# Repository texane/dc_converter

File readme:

updown DC converter. from 12V to 3.4V 5.2V 12V 19.6V.

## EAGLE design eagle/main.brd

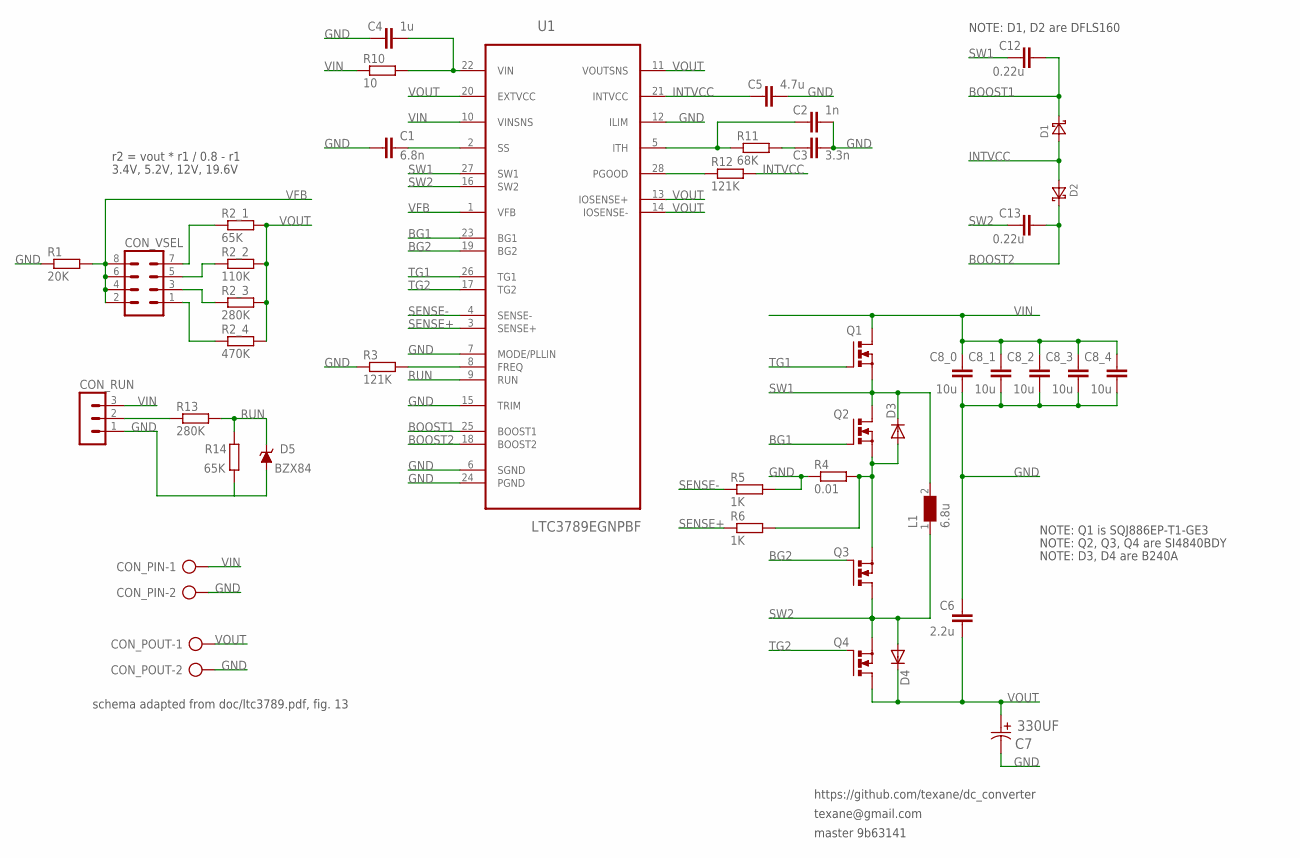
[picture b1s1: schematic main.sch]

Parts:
C1: 6.8n; C1206K
C2: 1n; C1206K
C3: 3.3n; C1206K
C4: 1u; C1206K
C5: 4.7u; C1206K
C6: 2.2u; C1206K
C7: 330UF; CAPAE1030X1050N
C8_0, C8_1, C8_2, C8_3, C8_4: 10u; C1206K
C12, C13: 0.22u; C1206K
CON_PIN: AK300/2
CON_POUT: AK300/2
CON_RUN: MA03-1
CON_VSEL: MA04-2
D1, D2: DIODE-SCHOTTKY-POWER-DI-123; POWER-DI-123
D3, D4: DIODE-DO214AC; DO214AC
D5: BZX84; SOT23
L1: 6.8u; WE-HCC_1210
Q1: SQJ886EP; POWERPAK-SO-08L
Q2, Q3, Q4: N-MOSFET-SO8S; SO-08
R1: 20K; R1206
R2_1, R14: 65K; R1206
R2_2: 110K; R1206
R2_3, R13: 280K; R1206
R2_4: 470K; R1206
R3, R12: 121K; R1206
R4: 0.01; R1206
R5, R6: 1K; R1206
R10: 10; R1206
R11: 68K; R1206
U1: LTC3789EGNPBF; SOP65P640X120-28N

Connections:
BG1: Q2.4 (G), U1.23 (BG1)
BG2: Q3.4 (G), U1.19 (BG2)
BOOST1: C12.2, D1.C, U1.25 (BOOST1)
BOOST2: C13.2, D2.C, U1.18 (BOOST2)
GND: C1.1, C2.2, C3.2, C4.1, C5.2, C6.2, C7.2, C8_0.2, C8_1.2, C8_2.2, C8_3.2, C8_4.2, CON_PIN.2, CON_POUT.2, CON_RUN.1, D5.1 (A), R1.1, R3.1, R4.1, R5.2, R14.1, U1.6 (SGND), U1.7 (MODE/PLLIN), U1.12 (ILIM), U1.15 (TRIM), U1.24 (PGND)
INTVCC: C5.1, D1.A, D2.A, R12.2, U1.21 (INTVCC)
unnamed: R3.2, U1.8 (FREQ)
unnamed: C4.2, R10.2, U1.22 (VIN)
unnamed: C1.2, U1.2 (SS)
unnamed: C2.1, R11.1, U1.5 (ITH)
unnamed: C3.1, R11.2
unnamed: R12.1, U1.28 (PGOOD)
unnamed: CON_VSEL.5, R2_2.1
unnamed: CON_VSEL.7, R2_1.1
unnamed: D3.A, Q2.1 (S), Q2.2 (S), Q2.3 (S), Q3.1 (S), Q3.2 (S), Q3.3 (S), R4.2, R6.2
unnamed: CON_VSEL.3, R2_3.1
unnamed: CON_RUN.2, R13.1
RUN: D5.3 (C), R13.2, R14.2, U1.9 (RUN)
SENSE+: R6.1, U1.3 (SENSE+)
SENSE-: R5.1, U1.4 (SENSE-)
SW1: C12.1, D3.C, L1.2, Q1.1 (S), Q1.2 (S), Q1.3 (S), Q2.5 (D), Q2.6 (D), Q2.7 (D), Q2.8 (D), U1.27 (SW1)
SW2: C13.1, D4.A, L1.1, Q3.5 (D), Q3.6 (D), Q3.7 (D), Q3.8 (D), Q4.1 (S), Q4.2 (S), Q4.3 (S), U1.16 (SW2)
TG1: Q1.4 (G), U1.26 (TG1)
TG2: Q4.4 (G), U1.17 (TG2)
VFB: CON_VSEL.1, CON_VSEL.2, CON_VSEL.4, CON_VSEL.6, CON_VSEL.8, R1.2, R2_4.1, U1.1 (VFB)
VIN: C8_0.1, C8_1.1, C8_2.1, C8_3.1, C8_4.1, CON_PIN.1, CON_RUN.3, Q1.5-8 (D), R10.1, U1.10 (VINSNS)
VOUT: C6.1, C7.1, CON_POUT.1, D4.C, Q4.5 (D), Q4.6 (D), Q4.7 (D), Q4.8 (D), R2_1.2, R2_2.2, R2_3.2, R2_4.2, U1.11 (VOUTSNS), U1.13 (IOSENSE+), U1.14 (IOSENSE-), U1.20 (EXTVCC)

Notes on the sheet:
schema adapted from doc/ltc3789.pdf, fig. 13
r2 = vout * r1 / 0.8 - r1
3.4V, 5.2V, 12V, 19.6V
NOTE: D3, D4 are B240A
NOTE: D1, D2 are DFLS160
NOTE: Q2, Q3, Q4 are SI4840BDY
NOTE: Q1 is SQJ886EP-T1-GE3
https://github.com/texane/dc_converter
texane@gmail.com
master 9b63141

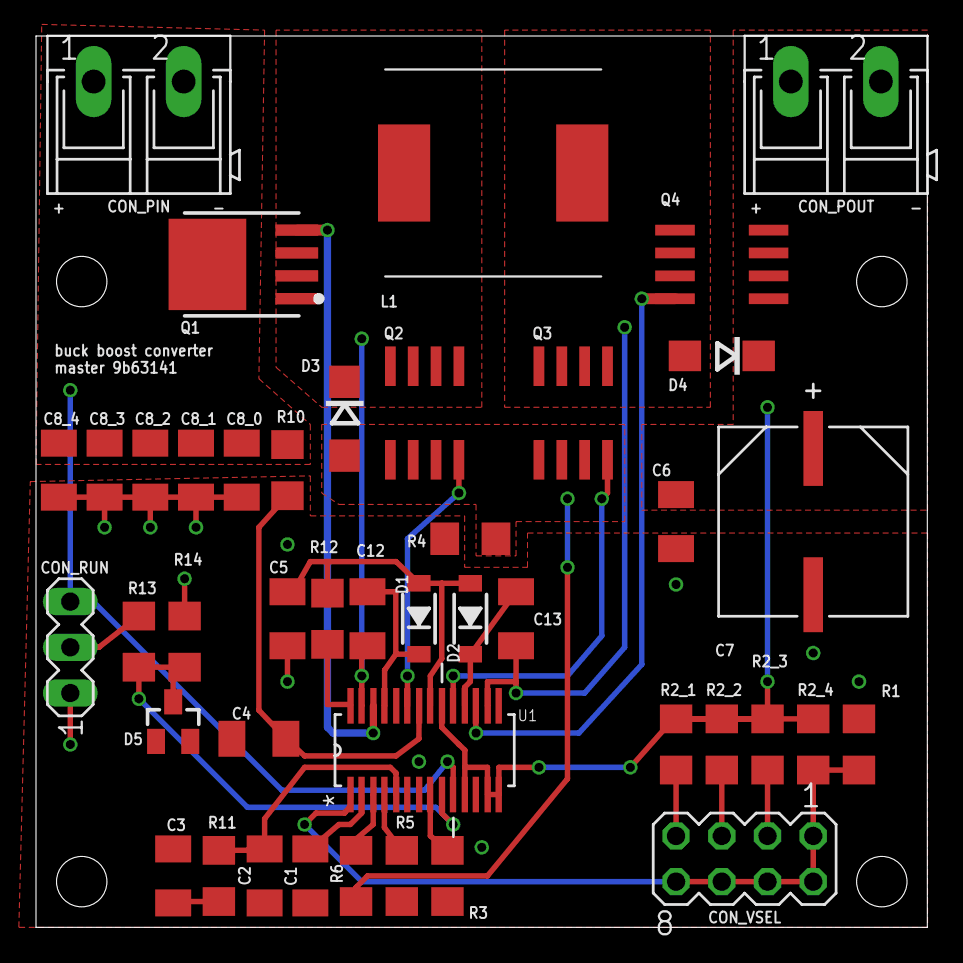
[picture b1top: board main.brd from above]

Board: 2 copper layers, 49.5 x 49.5 mm, 43 parts (0 on the bottom side), 27 nets.

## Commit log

2014-11-17 [ add ] readme
2014-11-17 [ add ] sch
2014-11-17 [ add ] doc/dn499.pdf, doc/ltc3789.pdf
2014-11-17 [ add ] ltspice/buck/main.asc
2014-11-17 [ update ] sch
2014-11-17 [ update ] mv sch to eagle
2014-11-18 [ add ] doc/dc1523af.pdf
2014-11-18 [ update, add ] eagle/main.brd
2014-11-18 [ add ] eagle/barthess_eagle_libs/transistor-fet.lbr
2014-11-18 [ add ] doc/ppakso8l.pdf
2014-11-18 [ add ] eagle/robertstarr_lbr_user/transistor-fet.lbr
2014-11-18 [ add ] doc/powerpak.pdf
2014-11-18 [ add ] Panasonic-EEEFT_EEEH\@E/Panasonic-EEEFT_EEEH.lbr
2014-11-19 [ add ] eagle/robertstarr_lbr_user/diode.lbr
2014-11-26 [ add ] gerber/main_master_9b63141.zip
2014-11-26 [ add ] eagle/main.pdf
2014-11-26 [ add ] boost.notes
2014-11-26 [ add ] ltspice/main.asc
2014-11-26 [ update ] boost.notes
2014-11-27 [ add ] doc/slva372c.pdf. contains boost related computations.
2014-11-27 [ add ] doc/slva061.pdf. TI AN on understanding boost power stages.
2014-11-27 [ add ] doc/High_Frequency_DC_DC_Boost_Converter_MQP_Final_Duka_Noble.pdf
2014-11-27 [ add ] ltc1871/main.asc
2014-11-27 [ update ] doc/boost.notes
2014-11-27 [ add ] buck.notes
2014-11-29 [ add ] doc/IJET13-05-01-070.pdf
2014-11-30 [ rename ] clean doc directory
2014-11-30 [ add ] ptmsect3.pdf
2014-11-30 [ update ] boost.notes, link
2014-11-30 [ add ] simonbramble_boost.pdf
